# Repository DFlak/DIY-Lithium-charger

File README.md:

# DIY Lithium charger

<b>First of all, I'm not in any way responsible for any damage that 
could be an outcome of using any part of this circuit.
Lithium batteries are dangerous and shouldn't be handled by unexperienced
persona. Never leave your packs unattended.</b>

I'm aiming to develop a cheap, safe, easy to build and multi-channel lithium charger.
Everyone knows that you can already buy things like iMax B6 clones or whatever. Simple answer is 
those chargers only allow you to charge one battery at a time and their balancing current is less than enough
for anyone that built a battery from used or mismatched cells.

Main goals:<b>

    Independent, balanced channels,
    Easy and cheap to expand,
    Possibly the smallest form factor,
    Wide input and output voltage range, 
    Making it safe to use.

Please remember that it is all work in progress.

## Balancer

The circuit used to build this balancer was created by Afdhal Atiff Tan Amin Husaini Tan from the http://www.afdhalatifftan.com/ blog. His work and his results inspired me to create a board from his schematic. The board uses 10mil trace width which is big enough for toner transfer and unskilled person and also plenty of spacing. The only thing worth mentioning is that resistors which form differential amplifier need to have 0.1% or less tolerance. I was succesful at buying 600pcs of 1k resistors from AliExpress and sorting them by using ADS1115 ADC. Basically you're looking for resistor closest to 1k value with a DMM and then you compare this resistor with any unknown 1k5% one. If value gets close enough LED blinks which indicates that its' resistance is close enough to be 1% tolerance. I can share the code and schematic if anyone needs it but its really basic. Sorting 600 resistors took me about 1,5h and yielded 47 1000+-1ohm and 12 1012+-1ohm resistors. 
A thing worth noting is that it doesn't matter if you choose 1012ohm resistors or 980ohm or whatever value. Only thing that matters is that those resistors need to be 0.1% or even closer to each other. 
I've created this design on regular FR4 1,6mm 35um copper clad. Initially I wanted to etch two sides on one-sided clads and then solder them together by vias but it ended up looking like crap and taking way more time that it needed. 
Will post updates with photos as I etch double-sided clad and test this circuit.
- [x] Create prototype PCB
- [x] Get really dissapointed with the results
- [ ] Order some double-sided PCBs
- [ ] Etch and prototype
- [ ] Post results

## The bare bones 

Basically this charger will push current into lithium packs using [LM2596 based step-down converters](https://www.aliexpress.com/item/1Pcs-LM2596S-DC-DC-Constant-Current-Module-LM2596-DC-DC-7V-35V-Step-down-Adjustable-CC/32849005778.html?spm=a2g0s.9042311.0.0.27424c4dF48BmC). They have usefull feature which is constant current mode and low drift floating voltage. However, them being step-down topology they need their Vin to be at least 2,5V greater than output. Anything lower than that can result in unstable operation of such converter. To remedy this problem I utilized [150W DC-DC Boost converter](https://www.aliexpress.com/item/150W-DC-DC-Boost-Converter-Step-Up-Power-Supply-Module-10-32V-To-12-35V-10A/2038554691.html?spm=a2g0s.9042311.0.0.27424c4dqFSutO) which is set to 19,5V, 2,7volts higher than full 4S Li-po pack. 
In order to stack the LM25965 converters I needed to change the orientation of trimpots from vertical to horizontal. It was done easily with a help of solder wick. Converters are held to each other via epoxy glue on top of the electrolytic capacitors. Heat didn't pose any issues while charging at 1.7A x3 packs. Neither LM25965 nor 150W boost converter were hot to the touch. 

I was powering this ciruit from diy-made 4s pack. 
The bare bones of this project are considered done. To expand this charger for more packs you would need to put more LM25965's in parallel keeping in mind the maximum of 150W for each boost converter. My estimate is that one boost converter can supply five charger modules.

## Control, safety and feedback

This charger will use Arduino Nano as a controller. Packs will be switched with a 5V RelPol relays. Each cell will be monitored using [CD74HC4067](https://www.aliexpress.com/item/Smart-Electronics-CD74HC4067-16-Channel-Analog-Digital-Multiplexer-Breakout-Board-Module-for-Arduino/32724398868.html?spm=a2g0s.9042311.0.0.61b64c4dKA2mvk), calibrated resistive voltage divider and [ADS1115 16bit ADC](https://www.aliexpress.com/item/I2C-ADS1115-ADS1015-16-Bit-ADC-4-channel-Module-with-Programmable-Gain-Amplifier-2-0V-to/32674556200.html?spm=2114.search0104.3.9.12472300DBfJgK&ws_ab_test=searchweb0_0,searchweb201602_4_10065_10068_10843_10059_5016517_10696_100031_5016717_10084_10083_10103_451_10618_452_10304_10307_5016617_10820_10301_10821_5016417,searchweb201603_45,ppcSwitch_5&algo_expid=fb968794-6da6-4dc2-80d7-a833cd81f520-1&algo_pvid=fb968794-6da6-4dc2-80d7-a833cd81f520&transAbTest=ae803_2&priceBeautifyAB=0). I'm planning on adding current monitoring but it all depends whether I can develop reliable and cheap low-side current meter without introducing any more losses. Voltage of each cell will be displayed on regular [16x2 LCD](https://www.aliexpress.com/item/1pcs-lot-New-1602-16x2-Character-LCD-Display-Module-HD44780-Controller-blue-blacklight-IN-STOCK/32328960211.html?spm=2114.search0104.3.2.56aa3c811IH5dc&ws_ab_test=searchweb0_0,searchweb201602_4_10065_10068_10843_10059_5016517_10696_100031_5016717_10084_10083_10103_451_10618_452_10304_10307_5016617_10820_10301_10821_5016417,searchweb201603_45,ppcSwitch_5&algo_expid=6a017778-b50d-4f92-a064-2eaae25a3f11-0&algo_pvid=6a017778-b50d-4f92-a064-2eaae25a3f11&transAbTest=ae803_2&priceBeautifyAB=0). Arduino will guard if every cell's voltage is in 3.2V < X > 4.2V range. Only then will it allow the relay to connect pack to the charger. Good idea would be to add a capacity meter, capacity limit and charging time limit. First two are dependant on my current meter so I don't know if it will be included.
- [x] Order all of the parts
- [ ] Receive all of the parts 
- [ ] Think of a way to measure current
- [ ] Create schematic
- [ ] Create .brd 
- [ ] Etch and prototype PCB
- [ ] Create arduino code
- [ ] Test the thing thoroughly
- [ ] Post all the files here

### If anyone is interested in helping me feel free to contact me via mail at wtflolrotfl@gmail.com :)

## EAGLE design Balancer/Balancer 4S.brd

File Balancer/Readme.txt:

The schematic was made by Afdhal Atiff Tan.
His blog can be found at this link and I encourage you to go take a look.

<b>http://www.afdhalatifftan.com/2017/06/low-cost-active-battery-balancer.html</b>

Board was made by me. It can be viewed by Eagle, I used version 7.7, resistors are THT because it's far easier to source 0.1% THT's than SMD's.

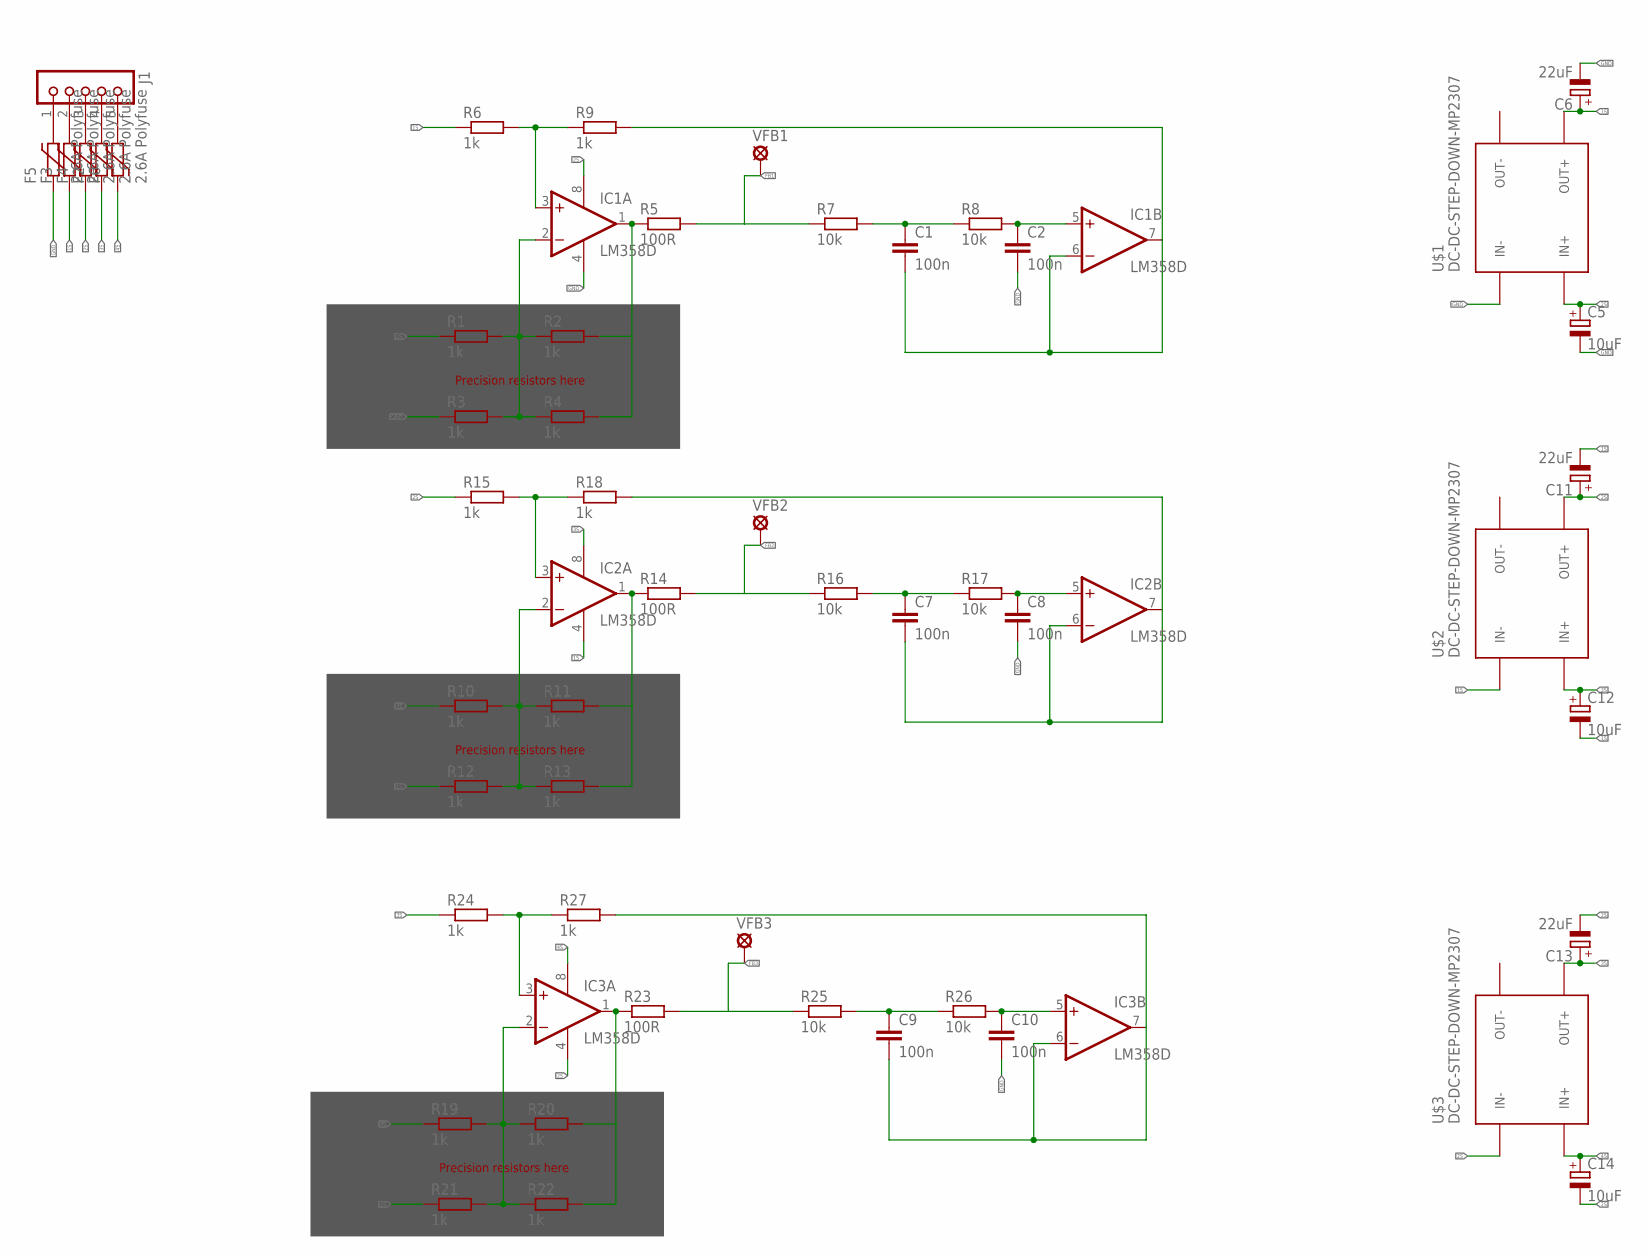
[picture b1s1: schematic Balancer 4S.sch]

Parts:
C1, C2, C7, C8, C9, C10: 100n; C0805K
C5, C12, C14: 10uF; E2,5-6E
C6, C11, C13: 22uF; E2,5-6E
F2, F3, F4, F5, F6: 2.6A Polyfuse; 1812L
IC1, IC2, IC3: LM358D; SO08
J1: JU05
R1, R2, R3, R4, R10, R11, R12, R13, R19, R20, R21, R22: 1k; 0204/7
R5, R14, R23: 100R; M0805
R6, R9, R15, R18, R24, R27: 1k; M0805
R7, R8, R16, R17, R25, R26: 10k; M0805
U$1, U$2, U$3: DC-DC-STEP-DOWN-MP2307
VFB1, VFB2, VFB3: MCS08

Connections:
1S: C6.+, C11.-, C12.-, F3.P$1 (1), IC2.4 (V-), R6.1, R12.1, U$1.OUT+, U$2.IN-
2S: C5.+, C11.+, C13.-, C14.-, F4.P$1 (1), IC1.8 (V+), IC3.4 (V-), R1.1, R15.1, R21.1, U$1.IN+, U$2.OUT+, U$3.IN-
3S: C12.+, C13.+, F2.P$1 (1), IC2.8 (V+), R10.1, R24.1, U$2.IN+, U$3.OUT+
4S: C14.+, F6.P$1 (1), IC3.8 (V+), R19.1, U$3.IN+
FB1: R5.2, R7.1, VFB1.MP
FB2: R14.2, R16.1, VFB2.MP
FB3: R23.2, R25.1, VFB3.MP
GND: C2.2, C5.-, C6.-, C8.2, C10.2, F5.P$1 (1), IC1.4 (V-), R3.1, U$1.IN-
unnamed: IC1.3 (+IN), R6.2, R9.1
unnamed: F5.P$2 (2), J1.1
unnamed: IC1.2 (-IN), R1.2, R2.1, R3.2, R4.1
unnamed: IC1.1 (OUT), R2.2, R4.2, R5.1
unnamed: C1.1, R7.2, R8.1
unnamed: C2.1, IC1.5 (+IN), R8.2
unnamed: C1.2, IC1.6 (-IN), IC1.7 (OUT), R9.2
unnamed: F4.P$2 (2), J1.3
unnamed: F3.P$2 (2), J1.2
unnamed: F2.P$2 (2), J1.4
unnamed: F6.P$2 (2), J1.5
unnamed: IC2.3 (+IN), R15.2, R18.1
unnamed: IC2.2 (-IN), R10.2, R11.1, R12.2, R13.1
unnamed: IC2.1 (OUT), R11.2, R13.2, R14.1
unnamed: C7.1, R16.2, R17.1
unnamed: C8.1, IC2.5 (+IN), R17.2
unnamed: C7.2, IC2.6 (-IN), IC2.7 (OUT), R18.2
unnamed: IC3.3 (+IN), R24.2, R27.1
unnamed: IC3.2 (-IN), R19.2, R20.1, R21.2, R22.1
unnamed: IC3.1 (OUT), R20.2, R22.2, R23.1
unnamed: C9.1, R25.2, R26.1
unnamed: C10.1, IC3.5 (+IN), R26.2
unnamed: C9.2, IC3.6 (-IN), IC3.7 (OUT), R27.2

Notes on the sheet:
Precision resistors here

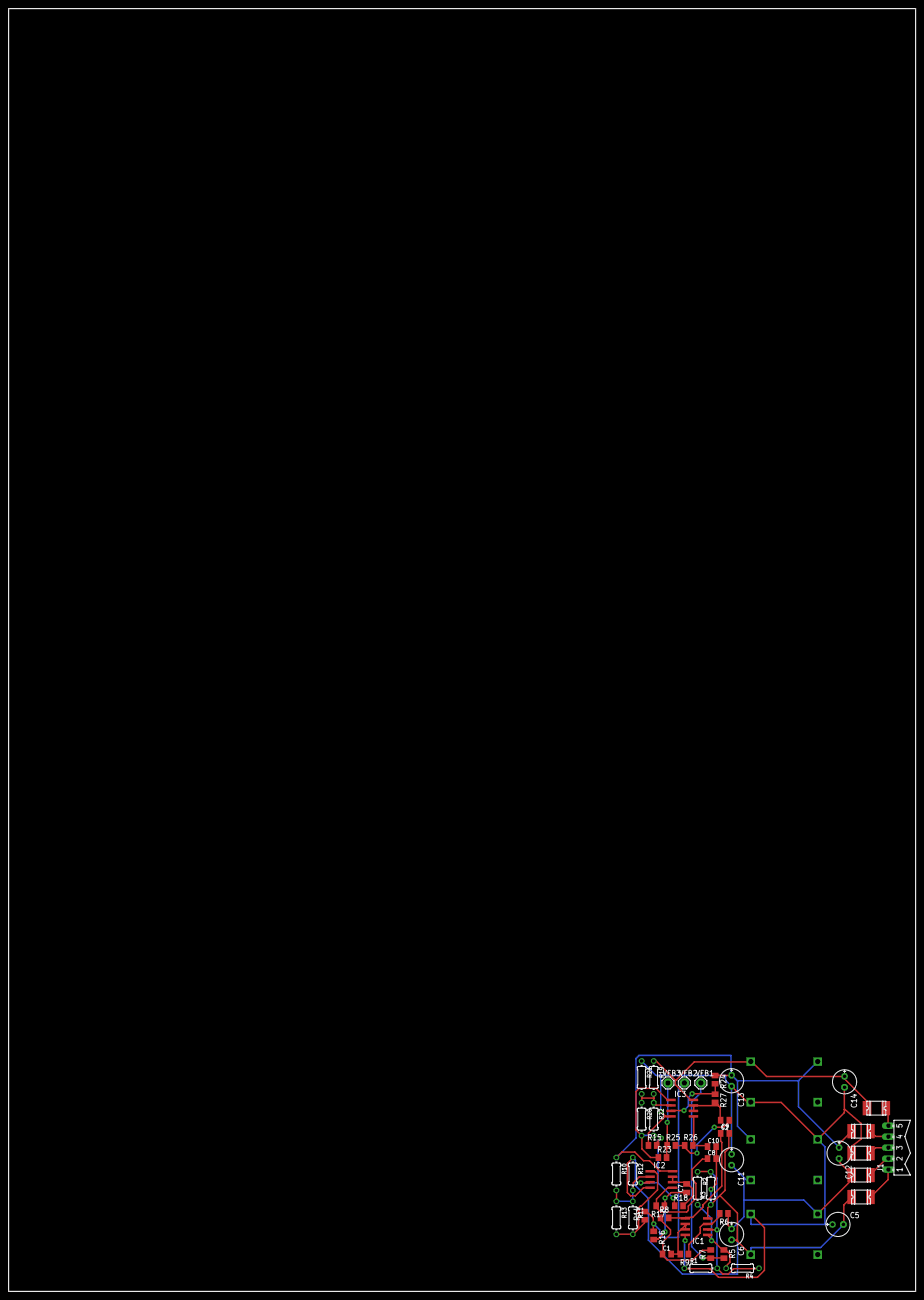
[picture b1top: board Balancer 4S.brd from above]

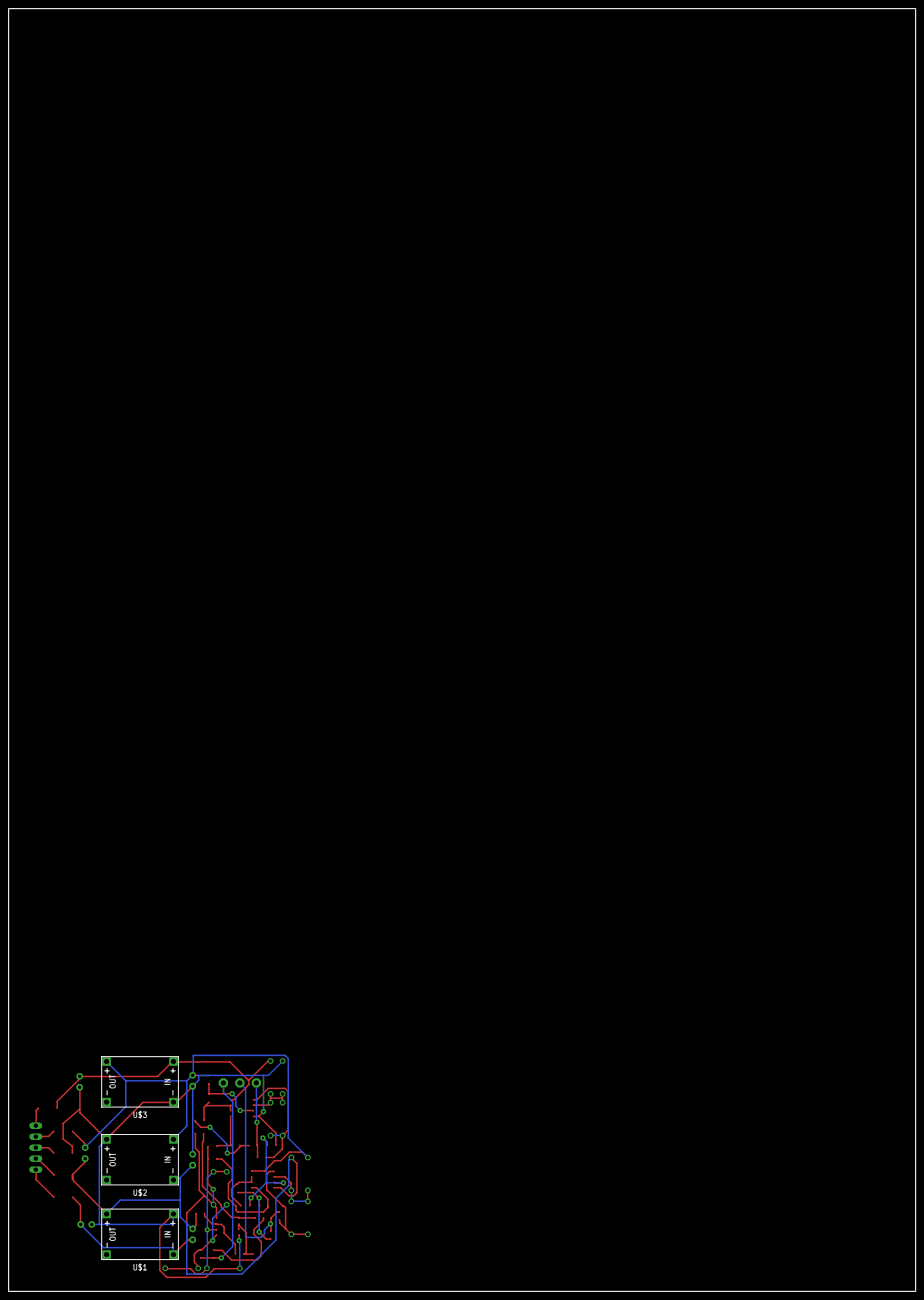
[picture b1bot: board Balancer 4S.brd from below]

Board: 2 copper layers, 210.0 x 297.0 mm, 54 parts (3 on the bottom side), 31 nets.

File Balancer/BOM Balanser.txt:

Partlist exported from C:/Users/Jabby/Desktop/Eagle/w trakcie/balanser/balanser 4s drugi prototyp, smd kondziorki.sch at 2018-09-01 18:04

Qty Value                  Device                 Package                Parts                                                  Description                                           MF MPN OC_FARNELL OC_NEWARK
1                          JU05                   JU05                   J1                                                     PIN HEADER                                                   unknown    unknown  
3   100R                   R-EU_M0805             M0805                  R5, R14, R23                                           RESISTOR, European symbol                                                        
6   100n                   C-EUC0805K             C0805K                 C1, C2, C7, C8, C9, C10                                CAPACITOR, European symbol                                                       
6   10k                    R-EU_M0805             M0805                  R7, R8, R16, R17, R25, R26                             RESISTOR, European symbol                                                        
3   10uF                   CPOL-EUE2,5-6E         E2,5-6E                C5, C12, C14                                           POLARIZED CAPACITOR, European symbol                                             
12  1k                     R-EU_0204/7            0204/7                 R1, R2, R3, R4, R10, R11, R12, R13, R19, R20, R21, R22 RESISTOR, European symbol                                                        
6   1k                     R-EU_M0805             M0805                  R6, R9, R15, R18, R24, R27                             RESISTOR, European symbol                                                        
5   2.6A Polyfuse          1812L                  1812L                  F2, F3, F4, F5, F6                                                                                                                      
3   22uF                   CPOL-EUE2,5-6E         E2,5-6E                C6, C11, C13                                           POLARIZED CAPACITOR, European symbol                                             
3   DC-DC-STEP-DOWN-MP2307 DC-DC-STEP-DOWN-MP2307 DC-DC-STEP-DOWN-MP2307 U$1, U$2, U$3                                          DC/DC Step-Down Regulator based on MP2307DN chip                                 
3   LM358D                 LM358D                 SO08                   IC1, IC2, IC3                                          OP AMP also LM158; LM258; LM2904                                                 
3   LSP10                  LSP10                  LSP10                  VFB1, VFB2, VFB3                                       SOLDER PAD drill 1.0 mm, distributor Buerklin, 12H555

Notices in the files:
parts and their libraries:
diy-modules: Released under the Creative Commons Attribution 4.0 International License: http://creativecommons.org/licenses/by/4.0
